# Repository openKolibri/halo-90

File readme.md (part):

![wornDynamic]

# HALO-90
A distinct ring of light. An ethereal glow. Patterns that ebb and flow to the music. Ninety lights. All controllable. Powered by a common coin cell. An engrossing look with retro vibes and a modern touch. This is HALO-90.

![presentedCase]

The *HALO* product series, in which these earrings ([HALO-90]) are the first item, is a fully open source electronic jewelery line. It is designed with elegance and wearability in mind. `90` refers to the ninety individually controllable LEDs on the earring face. The built-in compute power is also suitable for creating complex light shows.

This is the technical manual for anyone wanting to modify, hack, remix, or program their own light patterns onto the earrings. The manual goes into fine detail about construction, assembly, and firmware which should encompass all basic knowledge.

## Table of Contents
* [Design](#design)
  + [Hardware](#hardware)
    - [LEDs](#leds)
    - [Microcontroller](#microcontroller)
    - [Battery](#battery)
    - [Microphone](#microphone)
    - [Button](#button)
    - [IMU](#imu)
    - [Passives](#passives)
    - [Alignment Pins](#alignment-pins)
    - [Connectors](#connectors)
  + [Case](#case)
    - [FDM Printed](#fdm-printed)
    - [Cast](#cast)
      * [Mould Master](#mould-master)
      * [Silicone Mould](#silicone-mould)
    - [Stone Casting](#stone-casting)
    - [Magnets](#magnets)
* [Firmware](#firmware)
  + [Modes](#modes)
    - [Dynamic](#dynamic)
    - [Halo](#halo)
    - [Sparkle](#sparkle)
    - [Power Managment](#power-managment)
  + [LED control](#led-control)
  + [Compiling](#compiling)
    - [Ubuntu/WSL](#ubuntu-wsl)
    - [Arch](#arch)
  + [Flashing](#flashing)
    - [Windows](#windows)
    - [Linux](#linux)
* [Absolute Maximum Ratings](#absolute-maximum-ratings)
* [Guaranteed Ratings](#guaranteed-ratings)
* [Manufacturing](#manufacturing)
  + [BOM](#bom)
  + [PCB](#pcb)
  + [PCB Assembly](#pcb-assembly)
    - [Assembly Detail Pictures](#assembly-detail-pictures)
    - [Potential Alternates](#potential-alternates)
  + [Physical Assembly](#physical-assembly)
  + [Production Scaling](#production-scaling)
    - [Case](#case-1)
* [Programmer](#programmer)
* [Artwork](#artwork)
* [Inventory and QC](#inventory-and-qc)
* [Packaging](#packaging)
* [Shipping](#shipping)
* [Safety](#safety)
* [Certifications](#certifications)
* [Licence](#licence)
* [Attribution](#attribution)
  + [Fonts](#fonts)
  + [Libraries](#libraries)
* [ToDo](#todo)

## Design
Design was always a core objective from the very beginning. It *has* to look good. Even more importantly, it must also be functional, as it is a piece of jewelry people are going to wear. If it looks too complex or it's too difficult to use, no one will want to wear it. Comfort was also major goal, as heavy earrings are painful to wear for extended amounts of time, no matter how stunning they are. It's simply not worth the pain.

![render]

The design had to allow for a variety of LED patterns with a range from subtle to attention grabbing. Sensors were added to make light patterns more personal and reactive to the local environment, such as the muted audio responsive pattern. At one moment, befit for a quiet restaurant and later a flashy wide pattern at a concert.

| Audio        | Halo        | Sparkle        |
| ------------ | ----------- | -------------- |
| ![PAT-audio] | ![PAT-halo] | ![PAT-sparkle] |

### Hardware
The electronics are kept minimal for cost reduction and manufacturing simplicity with pads and routing done for all but the IMU and its pull-up resistors. They are not mounted, because there is no firmware support for that and it yields a lower cost variant. The design is done in [KiCad] 5.99 (nightly) and will be ported and set in the stable version. All components and libraries are embedded in the project. 

![IMG-schematic]

The schematic is also available as a [pdf][PDF-schematic]. The layout is done partially programmatically using text manipulation and template stamping using JavaScript and node and then finished up by hand in KiCad. The code is available [here][nodeHaloBuilding].

#### LEDs
There are 90 LEDs that make up the ring, All are regular `0402` red diodes. All the cathodes (K/-) face towards the center of the board, and are placed at `4°` intervals. The LEDS are charlieplexed with ten lines providing individual control. They are run at as high of a current as the battery's internal resistance and GPIO max current allows, so no resistors are used. The red LEDs, with their `2.0 V` - `2.6 V` forward voltage, permits maximizing battery usage
We are using [BL-HUB37A-AV-TRB], because it is low cost and has high availability across multiple vendors in China, but any `0402` LED with a V<sub>f</sub> below `2.7 V`, should yield an equivalent battery life.

![IMG-BL-HUB37A-AV-TRB]

#### Microcontroller
*STMicroelectonics's* [STM8L151G4] acts as the main controller for the earring. The low power microcontroller has a wide range of peripherals, a long expected production life, and low cost and availability in high quantities. Running at its max speed of `16 MHz` is able to easily charliplex the 90 Leds at over `1 kHz`. The `12b ADC` is used to readout the microphone and has plenty of flash (up to `32k`) to store an assortment of light patterns or complex processed designs.

![IMG-STM8151G6U6]

#### Battery
*Linx Technologies's* aptly named [BAT-HLD-001] is a stamped die-cut sheet-metal battery-holder that is as low profile as possible. It is sized for a `CR2032` lithium cell. The metal acts as the anode while the pad on the PCB is the cathode. Battery life varies based on what threshold for brightness you are content with. Over its lifetime, the internal resistance of the battery increases and the voltage decreases. This means that the current possible also decreases and thus the brightness.

![IMG-BAT-HLD-001]

#### Microphone
The microphone selection was rather difficult due to a lack of specifications available with amplified MEMS microphones. *Knowles* [SPW2430HR5H-B] was selected, as it seemed reasonable and could be tested with Adafruits breakout board fairly easily.

![IMG-SPW2430HR5H-B]

Using a built-in amplified MEMS microphone decreases the number of component placements and simplifies layout and verification, at the expense of not having instrumentation knowledge of your audio response.

#### Button
*C&K* [KXT3] series provides ultra low profile miniature tactile switches and we chose `KXT311LHS`, with a low actuation force of `100g`. It can be easily pressed with the edge of your nail, or a bit less comfortably with the back.

The button provides the functionality of changing light patterns by pressing and triggering it into a low power sleep mode by holding for `500 ms`. Completely available as an interrupt to the microcontroller, so other uses can be implemented. 

![IMG-KXT3]

#### IMU
[LSM6DSM] is a 6DOF IMU with a three-axis accelerometer and three-axis gyroscope by *STMicroelectronics*. It communicates over I2C and is connected to the hardware I2C peripheral in the microcontroller. It allows a fast data stream at very low power. It also has additional low power modes and the ability to wake the main microcontroller over interrupt with the routed interrupt pin. 

![IMG-LSM6DSM]

#### Passives
There are three passives (five if the IMU is populated) that can be of any tolerance. There are two `1 uF` and `0.1 uF` decoupling capacitors and one `10k` pull-up on the reset of the processor. The two IMU pull-ups are `10k` I2C pull-ups.

#### Alignment Pins
There are four tooling holes/alignment pins that can be used for add-ons. They are `1.152 mm` (`45.35 mil`) in diameter and are placed `2.8 mm` and `5.5 mm` from the center.

![alignmentPins]

 The earring is `24 mm` in diameter, has a mass of `5.207 g` (`2.135 g` without the battery) and the top eyelet extends `2 mm` extra, yielding a bounding box of `24 mm x 26 mm x 6.36 mm`.

![mass]

#### Connectors
The only connectors on the board are six `⌀ 1 mm` copper circles that are exposed as contacts for spring pins. They are placed evenly across the board so it receives balanced forces from the custom programmer (or testing jig).

| Labels      | Dimensions       |
| ----------- | ---------------- |
| ![pgrmPads] | ![pgrmPlacement] |

The labeled pins have their descriptions in the table below.

| Pin  | Description                      |
| ---- | -------------------------------- |
| 3V0  | Connected to Batt+ and power net |
| GND  | Connected to ground net          |
| TX   | GPIO PB2 for serial out          | 
| RX   | GPIO PB4 for serial in           | 
| RST  | Active low, 10k pull-up          | 
| SWIM | Programming interface            | 

### Case
The case holds the earrings and two cells in its cavities. This allows for the storing and organizing of at least 36 hours of available runtime. The earring case consists of two pieces held together with magnets. The cavities inside the case hold all components securely so that they do not rattle. The earrings are displayed beautifully when the case is opened.

![cases]

The case is designed in CAD and made to house two earrings (with or without batteries inserted) as well as two additional batteries. All of the edges are filleted and the closed case is comfortable when held. One corner is chamfered which makes it easier to align both pieces together in the correct orientation, and the magnets are oriented to resist trying to close it whenever the directionality does not match. It also provides a very satisfying tactile click when they align and close.

![caseRender]

#### FDM Printed
The first sets of cases are made of 3D printed plastic PLA. The top and bottom have bold contrasting colors that uniquely identify the brand. They are printed with a `20%` gyroid infill and at `200 um` layer height. The 3D models must be scaled up to `100.2%` to account for PLA shrinkage. 

![caseFDM]

#### Cast
For a more bold and distinctive style with a pebble or smooth seashell-like finish, casted cases provides an air of luxury using distinctive materials.

![caseBatch]

##### Mould Master
Moulding masters were made using the same 3D printed designs, printed at an `80 um` layer height, and then repeatedly filled, primed, and sanded with `P400` to `P3000` grit sandpaper on top of a glass plate to keep the straight faces square. This fills all of the air gaps and allows for a very smooth finish. It is then buffed to a shine with nail buffer sponges.

![caseMaster]

##### Silicone Mould
A platinum cure shore `A20` silicone rubber (Troll Factory [TYP-1]) is used to make a mould of the master. This has an accuracy of `~2 um` so it's able to reproduce a surface finish. Since the back is flat, an open-faced mould is made. The part, as well as the walls, are held in place with [Quakehold] museum wax, and mixing the exact amount of silicone needed (based on a CAD model) means a high yield. After curing, the mould box walls are cut off and the master is demoulded, yielding a silicone mould.

![caseMould]

#### Stone Casting
The mould can be cast with various materials, including other silicones, polyuretane, rubbers, and resins. In our case, we used plaster. We are using high compressive strength *Ernst Hinrichs* [Sockelgips FL] `Type-4 low expansion dental plaster`. These plasters have a thixotropic agent that allows them to flow better, which means that they mix thinner and reproduce in finer detail. Applying a surfactant to the mould, mixing with distilled water, and using a vibrating table produces castings with fewer bubbles. The back is roughly leveled off and set to cure. The part is demoulded and the back is hand finished with `P320-P3000` grit sandpaper.

![caseCasting]

After 24 hours, the part has cured to its final hardness and has dried out completely. It can then be processed further with magnets and dye. 

#### Magnets
The magnets are `6 mm x 1 mm` `N52` neodynium magnets that are glued in with UHU Max Repair Extreme adhesive. They are coated in `Ni-Cu-Ni`, at around `12 um`. The magnets are a very tight fit in their countersinks and are glued in to fit securely. They have a fixed orientation between both parts made, so swapping tops or bottoms with other sets is possible. There are few adhesives that work well when bonding two materials together that are already difficult to glue.

![6x1-magnets]

Magnets are installed using a gluing jig. One jig for the top and one for the bottom. Both jigs have magnets installed to correct for orientation when gluing. The jigs also have a matching chamfer which prevents the wrong part from being placed or placing the part backwards by accident.

![magnetsGlued]

The two jigs are color-coded as well. Adhesive is dispensed into the wells and the magnet is dropped, which automatically orients itself with the jig magnet. It can then be removed and set to cure.

![magnetJig]

## Firmware
The firmware is coded at the register level in C. The code is fully interrupt-based and performs quite efficiently. The toolchain is simple and built on open source tools. This makes it harder to code, but allows for significant optimization.
 
### Modes
There are multiple modes available on the halo earring that can be switched through when pressing the button. Each press of the button cycles to the next mode, eventually circling back around.

| Audio         | Halo        | Sparkle        |
| ------------- | ----------- | -------------- |
| ![GIF-audio]  | ![GIF-halo] | ![GIF-sparkle] |

#### Dynamic
The mode selected on startup is the audio-based dynamic mode. During every ADC cycle it reads the analog value and projects the audio waveform amplitude, based around a moving point on the ring with wrap around.

![PWR-audio]

Power profile readings show no correlation with audio level, and an `11.71 mA` power consumption with `105 uA` standard deviation. Projected battery life with a `220 mA` CR2032 cell is ~18.8 hours.

#### Halo
In the HALO mode, the entire light ring is lit. This is done through interlacing the illumination of each LED. The deep sleep auto wakeup timer is set to wake up every two clock cycles of the low speed `32 kHz` oscillator. On every wake, it changes to illuminate the 13th following LED, wrapping around at 90.

```c
setLed((prevLed + 13)%90);
```

This allows for a cleaner and more consistent scan over the entire halo ring since 13 is the greatest integer factor (besides 91), for all of the LEDs to be turned on evenly around the ring. Greater spacing causes *frames* to interlace with one another, resulting in a cleaner visual experience.

![PWR-halo]

Power profile readings show a `10.88 mA` power consumption with `60 uA` standard deviation. Projected battery life with a `220 mA` CR2032 cell is ~20.2 hours.

#### Sparkle
Sparkle mode is the best for minimal power draw and is implemented in a single line of code. At `~320 Hz`, the processor wakes from deep sleep and runs the selection of which LED to light (if any).

```c
rand()%15 ? ledLow(prevLed) : setLed(rand() % 90);
```

Given a 1/15 chance, a random LED will light up. Otherwise, any previously lit LEDs will be turned off. This results in a more visually pleasing pattern over just randomly lighting LEDs, which produce sharper bursts of light. Since the processor is only awake `0.002%` of the time, and the LED has a chance of being on only `6.6%` of the time, the power consumption is quite minimal. 

![PWR-sparkle]

Power profile readings show a `2.01 mA` power consumption with `327 uA` standard deviation. Projected battery life with a `220 mA` CR2032 cell is ~109.5 hours, (over 4.5 days).

#### Power Managment
Pressing and holding the button for `500 ms` will turn off all LEDs and put the cpu into deep sleep mode. In this mode the current draw is around `15 uA` and the only wake interrupt is the button press.

![GIF-boot]

Pressing and holding the button will show a boot-up animation that lights up in a ring around the face. Holding the button until it makes a full revolution, about one second, will trigger a software reset of the halo, turning it back on.

### LED control
Since the LEDs are configured in a charlieplex array, only one LED can be on at a time. Some optimization can allow multiple LEDs to light simultaneously, but at a cost of consistency in brightness and power draw. There are two low-level functions that can turn a individual LED on or off, as well as a helper function that remembers the last LED and turns it off before turning on the next one.

```c
void setLed(uint8_t led);
void ledHigh(uint8_t led);
void ledLow(uint8_t led);
```

The function to get the column and row from the LED number is shown below:
```c
uint8_t col = led / 9;
uint8_t topElements = 9 - col;
uint8_t row = 9 - (led % 9);
if (topElements <= (9 - row)) {
  row--;
}
```

To turn the LEDs off, the column and row are both set to high impedance. To turn it on, the column is set high and the row is set low.

The previous LED *must* be turned off before lighting up the next LED or else there is a risk of damaging the electronics. It is recommended to only use the `setLed` and `ledLow` functions.

### Compiling
Compiling is done with the [SDCC] ("Small Device C Compiler") and the included makefile.

As an example, the following steps are given for some systems but should easily be transferable to the distro of your choosing. The requirements are `make` and `sdcc`. They should both be available in the path. Once installation is completed, running `make` will generate the `halo.ihx` file, which is the binary to be flashed.

```bash
make
```

#### Ubuntu/WSL
```bash
sudo apt install -y make
sudo apt install -y sdcc
```
#### Arch
```bash
sudo pacman -S make
sudo pacman -S sdcc
```

### Flashing
Some form of flashing software is required, along with a programmer that can program over the `SWIM` protocol. We are using third party `STLink-V2` clones, because the form factor of the genuine programmer is difficult to use and newer programmers do not support `SWIM`.

#### Windows
`STVP_CmdLine` is required as the flashing software and comes with the software package [ST Visual Programmer]. This needs to be installed and `c/Program Files (x86)/STMicroelectronics/st_toolset/stvp/STVP_CmdLine.exe` needs to be added into the path.

Once it's installed, it can be run with the following flags. Preferably in WSL but should also be possible in CMD or PS.

```bash
STVP_CmdLine.exe -Device=STM8L15xG4 -FileProg=halo.ihx -verif -no_loop -no_log
```

It is also incorporated into the make file and can be run with the following:

```bash
make flash
```

#### Linux
[STM8 Flash] is an open source `SWIM` compatible flashing utility for linux. The tool is built from source. Short instructions are written below.

```bash
git clone https://github.com/vdudouyt/stm8flash.git
cd stm8flash
make
sudo make install
```

Flashing can then be done with the following command:

```bash 
stm8flash -cstlink -pstm8l151 -w halo.ihx
```

It is also incorporated into the make file and can be run with the following:

```bash
make flash
```

## Absolute Maximum Ratings

| Parameter         | Min  | Max | Unit |
| ----------------- | ----:| ---:| ---- |
| Battery Voltage   | -0.3 | 3.6 | Volt |
| Temperature       |  -40 |  85 | °C   |
| Power Draw        |  15u | 25m | Amp  |

## Guaranteed Ratings

| Parameter              | Min | Max | Unit |
| ---------------------- | ---:| ---:| ---- |
| Battery Voltage        | 1.8 | 3.6 | Volt |
| Operating Temperature  | -20 |  50 | °C   |
| Storage Temperature    | -40 |  85 | °C   |

The earrings should be fine to leave in a hot car (although the 3D printed plastic case could warp). If you are outside of these ratings, take care of yourself, you are either freezing or at risk of heat stroke. The earrings will be fine.

## Manufacturing
Although taking on novel uses of materials, the ability to manufacture at scale was always a primary focus. Parts were selected with strong supply chains and alternatives. Layout was designed with generous rules to accommodate for as many fabs as possible and the number of unique components was minimized. The microphone and battery holder are from single vendors but they have proven track records and well-known supply chains. Alternatives to be tested are still proposed.

### BOM
The BOM was selected with parts that are common to the high-volume Chinese manufacturing market, have strong supply chains, and have many alternatives available in case a supplier stops manufacture or supply dips occur. The number of unique parts was kept to a minimum and the maximum amount of features can be implemented with "free" pins, like the programming SMD pads. The table of BOM is shown below.

| REF    | QTY | Manufacturer              | MPN              | Description                         |
| ------ | ---:| ------------------------- | ---------------- | ----------------------------------- |
| D1-D90 |  90 | Brightled                 | BL-HUB37A-AV-TRB | LED: RED 627-637nm 50mcd@20mA 0402  |
| U1     |   1 | STMicroelectronics        | STM8L151G4U6     | MCU: 8b 16MHz 16k Flash UQFN-28-4x4 |
| MK1    |   1 | Knowles Electronics       | SPW2430HR5H-B    | MIC: Omni Si-Sonic 3.1x2.5x1.0mm    |
| BT1    |   1 | Linx Technologies         | BAT-HLD-001      | BAT: CR2032 Cell Holder             |
| S1     |   1 | C&K                       | KXT311LHS        | SW: Low Profile 3x2x0.6mm 100gf     |
| R3     |   1 | Uniroyal                  | 0402WGF1002TCE   | RES: 10k 5% 1/16W 0402              |
| C1     |   1 | Samsung Electro-Mechanics | CL05B104KO5NNNC  | CAP: MLCC 100nF 16V 0402            |
| C2     |   1 | Samsung Electro-Mechanics | CL05A105KA5NQNC  | CAP: MLCC 1uF 25V 0402              |

The [csv][BOMcsv] is provided with the sources.

### PCB
There is a single PCB. Although still common, some of the more precise requirements were needed to end up with a printed circuit board small enough.

| Parameter          | Value | Unit |
| ------------------ | -----:| ---- |
| Height             |    26 | mm   |
| Width              |    24 | mm   |
| Layers             |     4 | ul   |
| Copper             |   1.0 | oz   |
| Copper Inner       |   0.5 | oz   |
| Thickness          |   1.0 | mm   |
| Material           | FR4   | ul   |
| Min Drill          |   0.2 | mm   |
| Trace Size         |   5/5 | mil  |
| Mask               | Black | ul   |
| Silk               | White | ul   |
| E-Test             | Yes   | ul   |
| Surface Finish     | ENIG  | ul   |

The PCB has four layers.

| Front     | Inner 1   | Inner 2   | Back      |
| --------- | --------- | --------- | --------- |
| ![Layer0] | ![Layer1] | ![Layer2] | ![Layer3] |

### PCB Assembly
The whole board can be pick and placed. The table below shows some data that might be needed when requesting a quote.

| Parameter         | Value |
| ----------------- | -----:|
| Unique Parts      |     8 |
| SMD Parts         |     8 |
| Placements        |    97 |
| Solder Joints     |   222 |
| Front Components  |    96 |
| Back Components   |     1 |

The smallest components are `0402` LEDs, and all parts can survive normal lead-free re flow profiles. The microphone is open port MEMS so do not wash, clean, or expose it to ultrasonic vibrations (datasheet has further requirements).

#### Assembly Detail Pictures

| Assembly    | Front       |
| ----------- | ----------- |
| ![assembly] | ![front]    |

| Front Detail   | Back Detail   |
| -------------- | ------------- |
| ![frontDetail] | ![backDetail] |

| Front ISO   | Back ISO    |
| ----------- | ----------- |
| ![frontIso] | ![backIso]  |

#### Potential Alternates
Some alternates have not been tested, but their specifications match.

| Stated            | Alternative      | Tested |
| ----------------- | ---------------- | ------ |
| SPW2430HR5H-B     | ZILLTEK ZTS6016  | No     |
| BAT-HLD-001       | MY-2032-08       | No     |
| STM8L151G4U6      | STM8L151G6U*     | Yes    |

*To be updated when I can get stock or have to switch suppliers*

### Physical Assembly

The earwire is attached with jewelry pliers through the hole. The 1mm hole is made for up to `0.8 mm` wire over `20 ga`. Gold plated french hooks are used. these are commonly available as jewelry findings.

![IMG-frenchEarwire]

### Production Scaling Boards
The board can be hexagonally packed into a panel with tiny tabs since it's held on all sides. To increase production efficiency, only one side can be PnP and the battery holder is added afterwards by hand.

![hexPackedPanel]

#### Production Scaling Cases
The master moulds can create secondary masters out of resin which could then be used to make gang moulds, allowing for multiple castings in parallel. 

![gangMoulds]

## Programmer
The programmer has a hole at the top to allow a pin to push the button for testing.

![programmer]

The 3D printed base holds the board in place while the PCB is held to it with 3mm heat set inserts. The PCB acts as a compliant mechanism providing down pressure while still allowing it to be flexible enough to lift. 

The programmer uses *Mill-Max* ‎‎‎[0965-0-15-20-80-14-11-0]‎ spring pins on a PCB that matches exactly with the six pads on the face of the board. 

![springPins]

The top part is lifted up and the assembled board is slipped in. The spring force from the PCB pushes back down on to the pads and can then be left for programming and debugging.

## Artwork
The design and layout, the main artwork on the board and the PCB layers and traces, are *NOT* protected Intellectual Property ("IP"), see LICENSE files for appropriate details.
Any additional writing or images such as the Kolibri bird, copyright and designer notices, and certifications *ARE* considered protected IP and notice is given that they are protected by all applicable IP laws.
The below "Getting Started" card also has artwork which is considered protected IP and is copyrighted with all rights reserved.

| Front        | Back        |
| ------------ | ----------- |
| ![cardFront] | ![cardBack] | 

## Inventory and QC
Inventory can be managed with QR coded serialized tags. This serialization provides better quality control because it allows failure analysis and tracking in cases of issues traceable to batch and assembly.

## Packaging
We are packaging and shipping in `14 cm x 17 cm` padded envelopes with branded stampings. These fit under the Warenpost requirements and allow international shipping. The envelopes are verified to be under `3 cm` before dispatching. Custom labeled sleeves will be used for retail packaging.

## Shipping
The labels are printed with CN22 on the harmonized label schedule.

Lithium cells have special requirements for shipping. With air mail, small cells (up to four) are packaged securely and may be sent with the product. A note (`Lithium metal batteries in compliance with Section II of PI969`) is required on the packaging, but no warning label is mandatory.

For international shipping, the HS code `7117.90.0000	Imitation Jewlery other` is used.

## Safety
The edges are fully routed when possible or finished afterwards. The PCB is made from fiberglass so care must be taken because it can have abrasive edges. Clear coat nail polish can be applied to round and soften the edges without changing how it looks.

The `CR2032` cells are quite safe, as they have only very small traces of lithium, and have a fairly high internal resistance. However, they must still be disposed of responsibly. `LIR2032` or other rechargeable 2032 cells should *not* be used because they have a higher voltage outside of the guaranteed parameters and significantly lower capacity (under 25%).

If the battery is placed in backwards, it will drain over time because there is no reverse polarity protection. It will heat up but should not damage anything, due to high internal resistance limiting the discharge. The low voltage, `3.0 V`, as well as the currents used pose very little risk.

The printed circuit boards are assembled in a lead-free process, and all components are `ROHS` certified.

## Certifications
Certifications take time and effort but will make a better product by guaranteeing its safety to users and letting them use it in other projects. The table below shows the order in which we will obtain certifications.

| Certifying Authority     | Status                    |
| -------------------------| ------------------------- |
| OSHW                     | [DE000103]                |
| CE                       | No  (Self Certification)  |
| FCC                      | No  (Self Certification)  |
| WEEE                     | No  (yearly fee)          |

## Licence
The product was designed by Sawaiz Syed for Kolibri. Kolibri owns all protected IP. Everything that is not otherwise stated as being protected IP (e.g. firmware, PCB design, documentation) is released under permissive copyleft licenses.

| Sector        | License      | Version |
| ------------- | ------------ | -------:|
| Hardware      | [CERN-OHL-S] |     2.0 |
| Firmware      | [GNU GPL]    |     3.0 |
| Documentation | [CC BY-SA]   |     4.0 |

Files of all licenses are required with the distribution of files. All files are available in easy-to-modify formats for remixing. 

---
#### Please purchase original products from [Kolibri] to support further products, design, and research :)

---

## Attribution
- Make
- [SDCC]
- KiCad
- [STM8Flash]
### Fonts
- [Nunito]
- [IBM PLEX Mono]
- [DejaVu] 
### Libraries
- [STM8 Headers] Copyright (c) - 2020 Georg Icking-Konert

## ToDo
- [x] Led sometimes remains on after shutdown
- [x] Randomly HALO pattern forms high low pattern

<!--                       References                                      -->
<!-- Files -->
[BAT-HLD-001]:                ./pcb/components/BAT-HLD-001/BAT-HLD-001.pdf
[BL-HUB37A-AV-TRB]:           ./pcb/components/BL-HUB37A-AV-TRB/BL-HUB37A-AV-TRB.pdf
[KXT3]:                       ./pcb/components/KXT3/KXT3.pdf
[LSM6DSM]:                    ./pcb/components/LSM6DSM/LSM6DSM.pdf
[SPW2430HR5H-B]:              ./pcb/components/SPW2430HR5H-B/SPW2430HR5H-B.pdf
[STM8L151G4]:                 ./pcb/components/STM8151G6U6/STM8151G6U6.pdf
<!-- Links -->
[HALO-90]:                    https://openkolibri.com/hlo/90
[KiCad]:                      https://kicad.org/
[ST Visual Programmer]:       https://www.st.com/en/development-tools/stvp-stm32.html
[Quakehold]:                  https://www.quakehold.com/collectibles.html
[TYP-1]:                      https://trollfactory.de/produkte/silikon-kautschuk/haertegrad-shore/weich-shore-a25/7044/tfc-silikon-kautschuk-typ-1-abformsilikon-weich-1-1-nv-troll-factory-rtv
[0965-0-15-20-80-14-11-0]:    https://www.mill-max.com/products/pin/0965
[Sockelgips FL]:              https://www.hinrichs-dental-shop.de/sockelgips-fl-p-1469.html
[Kolibri]:                    https://openkolibri.com/
<!-- Internal Links -->
[PDF-schematic]:              ./docs/design/hardware/schematic.pdf        
[nodeHaloBuilding]:           ./pcb/halo.js
[BOMcsv]:                     ./pcb/bom.csv
<!-- Intro -->
[wornDynamic]:                ./docs/intro/wornDynamic.gif                              "Worn earring reacting to music Model: Greta"
[presentedCase]:              ./docs/intro/haloSetDisplay.jpg                           "Pair of earings in holder"
[render]:                     ./docs/render.jpg                                         "Render of earrings showing propertions"
<!-- Design -->
[PAT-audio]:                  ./docs/patterns/audio.gif                                 "Worn animation of audio pattern"
[PAT-halo]:                   ./docs/patterns/halo.gif                                  "Worn animation of halo pattern"
[PAT-sparkle]:                ./docs/patterns/sparkle.gif                               "Worn animation of sparkle pattern"
<!-- Hardware -->
[IMG-schematic]:              ./docs/design/hardware/schematic.png                      "Image of schematic"

<!-- Components -->
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
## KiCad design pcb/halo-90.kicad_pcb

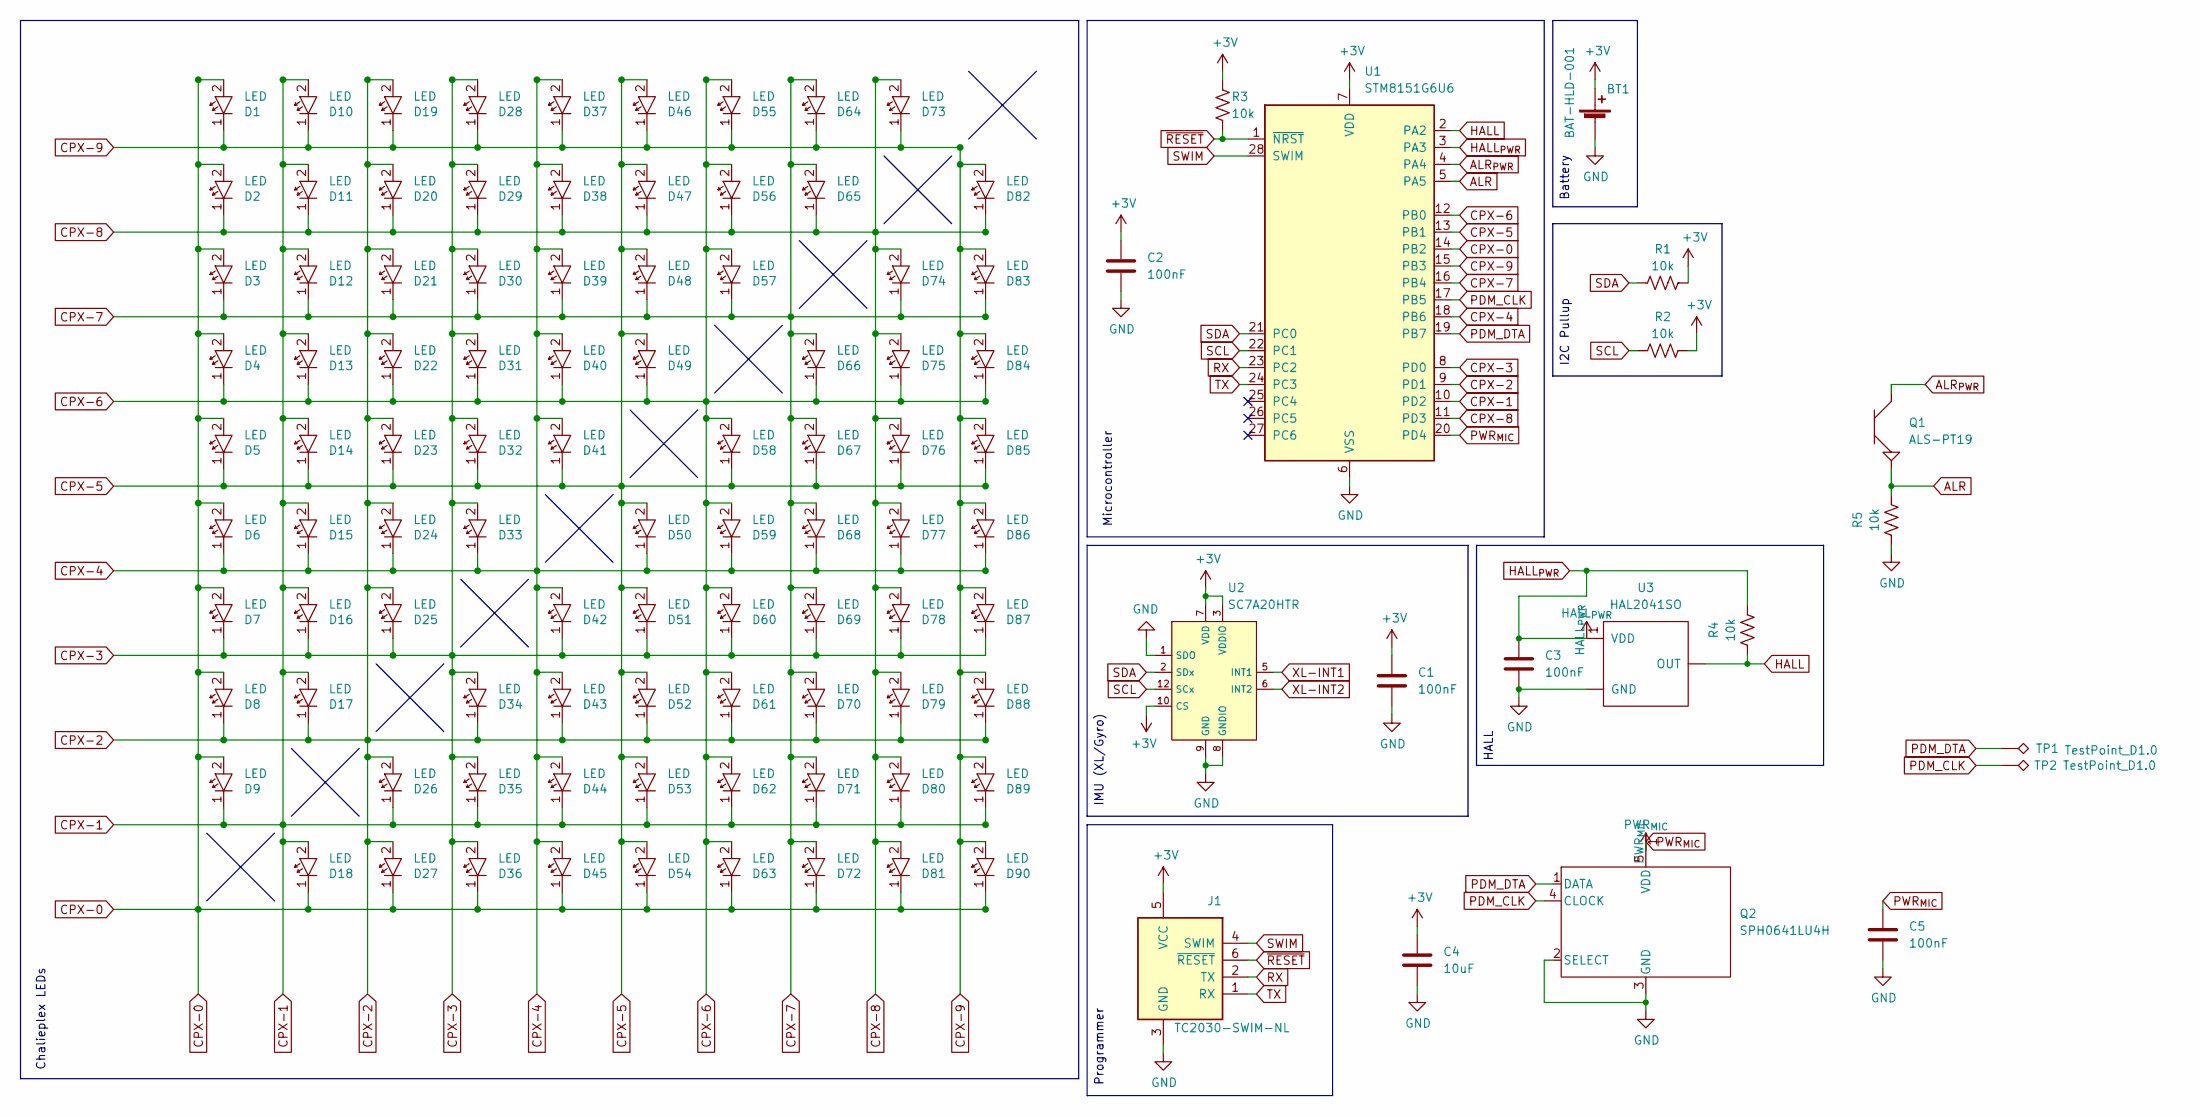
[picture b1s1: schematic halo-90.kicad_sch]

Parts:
BT1: BAT-HLD-001; LCSC Part # C7501066
C1, C2, C3, C5: 100nF; C-0402; MPN CL05B104KO5NNNC; LCSC Part # C1525
C4: 10uF; C-0402; MPN CL05A106MQ5NUNC; LCSC Part # C15525
D1, D2, D3, D4, D5, D6, D7, D8, D9, D10, D11, D12, D13, D14, D15, D16, D17, D18, D19, D20, D21, D22, D23, D24, D25, D26, D27, D28, D29, D30, D31, D32, D33, D34, D35, D36, D37, D38, D39, D40, D41, D42, D43, D44, D45, D46, D47, D48, D49, D50, D51, D52, D53, D54, D55, D56, D57, D58, D59, D60, D61, D62, D63, D64, D65, D66, D67, D68, D69, D70, D71, D72, D73, D74, D75, D76, D77, D78, D79, D80, D81, D82, D83, D84, D85, D86, D87, D88, D89, D90: LED; XL-1005SURC; MPN XL-1005SURC; LCSC Part # C25503345
J1: TC2030-SWIM-NL; TC2030-IDC-NL
Q1: ALS-PT19; MPN ALS-PT19-315C/L177/TR8; LCSC Part # C146233
Q2: SPH0641LU4H; MPN SPH0641LU4H-1; LCSC Part # C2879853
R1, R2, R3, R4, R5: 10k; R-0402; MPN 0402WGF1002TCE; LCSC Part # C25744
TP1, TP2: TestPoint_D1.0; TestPoint_Pad_D1.0mm
U1: STM8151G6U6; UFQFPN28; MPN STM8151G6U6; LCSC Part # C85325
U2: SC7A20HTR; MPN SC7A20HTR; LCSC Part # C19274408
U3: HAL2041SO; MPN HAL2041SO; LCSC Part # C22400320

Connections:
+3V: BT1.1 (+), C1.1, C2.1, C4.1, J1.5 (VCC), R1.2, R2.2, R3.1, U1.7 (VDD), U2.3 (VDDIO), U2.7 (VDD), U2.10 (CS)
ALR: Q1.2 (Emitter), R5.2, U1.5 (PA5)
ALR_{PWR}: Q1.1 (Collector), U1.4 (PA4)
CPX-0: D1.2 (K), D2.2 (K), D3.2 (K), D4.2 (K), D5.2 (K), D6.2 (K), D7.2 (K), D8.2 (K), D9.2 (K), D18.1 (A), D27.1 (A), D36.1 (A), D45.1 (A), D54.1 (A), D63.1 (A), D72.1 (A), D81.1 (A), D90.1 (A), U1.14 (PB2)
CPX-1: D9.1 (A), D10.2 (K), D11.2 (K), D12.2 (K), D13.2 (K), D14.2 (K), D15.2 (K), D16.2 (K), D17.2 (K), D18.2 (K), D26.1 (A), D35.1 (A), D44.1 (A), D53.1 (A), D62.1 (A), D71.1 (A), D80.1 (A), D89.1 (A), U1.10 (PD2)
CPX-2: D8.1 (A), D17.1 (A), D19.2 (K), D20.2 (K), D21.2 (K), D22.2 (K), D23.2 (K), D24.2 (K), D25.2 (K), D26.2 (K), D27.2 (K), D34.1 (A), D43.1 (A), D52.1 (A), D61.1 (A), D70.1 (A), D79.1 (A), D88.1 (A), U1.9 (PD1)
CPX-3: D7.1 (A), D16.1 (A), D25.1 (A), D28.2 (K), D29.2 (K), D30.2 (K), D31.2 (K), D32.2 (K), D33.2 (K), D34.2 (K), D35.2 (K), D36.2 (K), D42.1 (A), D51.1 (A), D60.1 (A), D69.1 (A), D78.1 (A), D87.1 (A), U1.8 (PD0)
CPX-4: D6.1 (A), D15.1 (A), D24.1 (A), D33.1 (A), D37.2 (K), D38.2 (K), D39.2 (K), D40.2 (K), D41.2 (K), D42.2 (K), D43.2 (K), D44.2 (K), D45.2 (K), D50.1 (A), D59.1 (A), D68.1 (A), D77.1 (A), D86.1 (A), U1.18 (PB6)
CPX-5: D5.1 (A), D14.1 (A), D23.1 (A), D32.1 (A), D41.1 (A), D46.2 (K), D47.2 (K), D48.2 (K), D49.2 (K), D50.2 (K), D51.2 (K), D52.2 (K), D53.2 (K), D54.2 (K), D58.1 (A), D67.1 (A), D76.1 (A), D85.1 (A), U1.13 (PB1)
CPX-6: D4.1 (A), D13.1 (A), D22.1 (A), D31.1 (A), D40.1 (A), D49.1 (A), D55.2 (K), D56.2 (K), D57.2 (K), D58.2 (K), D59.2 (K), D60.2 (K), D61.2 (K), D62.2 (K), D63.2 (K), D66.1 (A), D75.1 (A), D84.1 (A), U1.12 (PB0)
CPX-7: D3.1 (A), D12.1 (A), D21.1 (A), D30.1 (A), D39.1 (A), D48.1 (A), D57.1 (A), D64.2 (K), D65.2 (K), D66.2 (K), D67.2 (K), D68.2 (K), D69.2 (K), D70.2 (K), D71.2 (K), D72.2 (K), D74.1 (A), D83.1 (A), U1.16 (PB4)
CPX-8: D2.1 (A), D11.1 (A), D20.1 (A), D29.1 (A), D38.1 (A), D47.1 (A), D56.1 (A), D65.1 (A), D73.2 (K), D74.2 (K), D75.2 (K), D76.2 (K), D77.2 (K), D78.2 (K), D79.2 (K), D80.2 (K), D81.2 (K), D82.1 (A), U1.11 (PD3)
CPX-9: D1.1 (A), D10.1 (A), D19.1 (A), D28.1 (A), D37.1 (A), D46.1 (A), D55.1 (A), D64.1 (A), D73.1 (A), D82.2 (K), D83.2 (K), D84.2 (K), D85.2 (K), D86.2 (K), D87.2 (K), D88.2 (K), D89.2 (K), D90.2 (K), U1.15 (PB3)
GND: BT1.2 (-), C1.2, C2.2, C3.2, C4.2, C5.2, J1.3 (GND), Q2.2 (SELECT), Q2.3 (GROUND), R5.1, U1.6 (VSS), U2.1 (SDO), U2.8 (GNDIO), U2.9 (GND), U3.3 (GND)
HALL: R4.1, U1.2 (PA2), U3.2 (OUT)
HALL_{PWR}: C3.1, R4.2, U1.3 (PA3), U3.1 (VCC)
PDM_CLK: Q2.4 (CLOCK), TP2.1 (1_1), U1.17 (PB5)
PDM_DTA: Q2.1 (DATA), TP1.1 (1_1), U1.19 (PB7)
PWR_{MIC}: C5.1, Q2.5 (V_{DD}), U1.20 (PD4)
RX: J1.2 (TX), U1.23 (PC2)
SCL: R2.1, U1.22 (PC1), U2.12 (SCx)
SDA: R1.1, U1.21 (PC0), U2.2 (SDx)
SWIM: J1.4 (SWIM), U1.28 (SWIM)
TX: J1.1 (RX), U1.24 (PC3)
XL-INT1: U2.5 (INT1)
XL-INT2: U2.6 (INT2)
~RESET: J1.6 (~RESET), R3.2, U1.1 (~NRST)

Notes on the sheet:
IMU (XL/Gyro)
Battery
Microcontroller
HALL
I2C Pullup
Chalieplex LEDs
Programmer

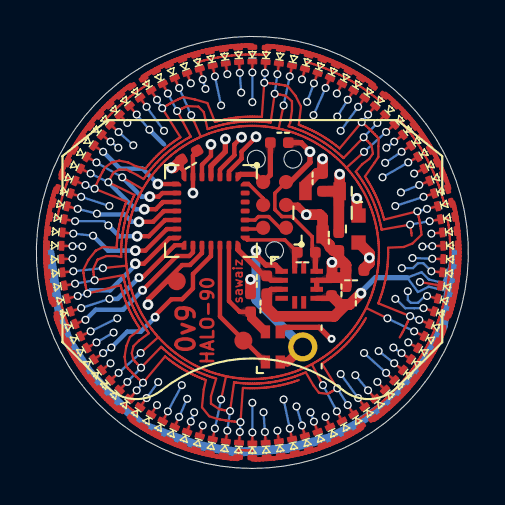
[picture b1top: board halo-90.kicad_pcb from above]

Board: 4 copper layers, 24.0 x 24.0 mm, 109 parts (1 on the bottom side), 25 nets.

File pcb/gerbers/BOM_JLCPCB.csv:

"Comment","Designator","Footprint","LCSC Part #"
"CR-2032","BT1","BAT-HLD-001:BAT-HLD-001","C7501066"
"10uF","C4","C-0402:C-0402","C15525"
"100nF","C1,C2,C3","C-0402:C-0402","C1525"
"LED","D1,D2,D3,D4,D5,D6,D7,D8,D9,D10,D11,D12,D13,D14,D15,D16,D17,D18,D19,D20,D21,D22,D23,D24,D25,D26,D27,D28,D29,D30,D31,D32,D33,D34,D35,D36,D37,D38,D39,D40,D41,D42,D43,D44,D45,D46,D47,D48,D49,D50,D51,D52,D53,D54,D55,D56,D57,D58,D59,D60,D61,D62,D63,D64,D65,D66,D67,D68,D69,D70,D71,D72,D73,D74,D75,D76,D77,D78,D79,D80,D81,D82,D83,D84,D85,D86,D87,D88,D89,D90","XL-1005SURC:XL-1005SURC","C25503345"
"TC2030-SWIM-NL","J1","TC2030-IDC-NL:TC2030-IDC-NL",""
"10k","R1,R2,R3,R4","R-0402:R-0402","C25744"
"STM8151G6U6","U1","STM8151G6U6:UFQFPN28","C85325"
"SC7A20HTR","U2","SC7A20HTR:SC7A20HTR","C19274408"
"HAL2041SO","U3","HAL2041SO:HAL2041SO","C22400320"

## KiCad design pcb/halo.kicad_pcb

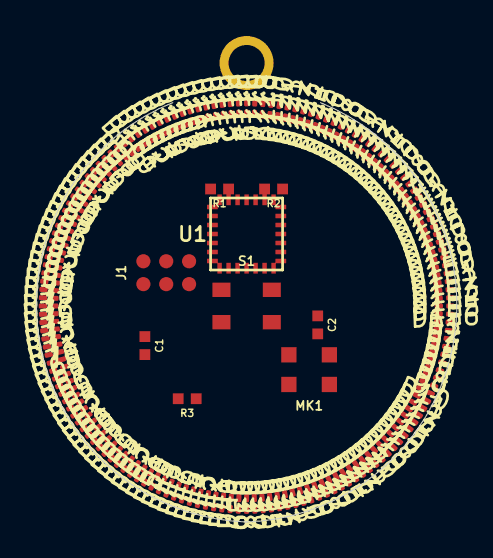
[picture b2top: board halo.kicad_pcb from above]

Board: 4 copper layers, 23.4 x 23.3 mm, 166 parts (0 on the bottom side), 22 nets, no tracks yet.

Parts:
C1, C2: C-0402
D1, D2, D3, D4, D5, D6, D7, D8, D9, D10, D11, D12, D13, D14, D15, D16, D17, D18, D19, D20, D21, D22, D23, D24, D25, D26, D27, D28, D29, D30, D31, D32, D33, D34, D35, D36, D37, D38, D39, D40, D41, D42, D43, D44, D45, D46, D47, D48, D49, D50, D51, D52, D53, D54, D55, D56, D57, D58, D59, D60, D61, D62, D63, D64, D65, D66, D67, D68, D69, D70, D71, D72, D73, D74, D75, D76, D77, D78, D79, D80, D81, D82, D83, D84, D85, D86, D87, D88, D89, D90, D91, D92, D93, D94, D95, D96, D97, D98, D99, D100, D101, D102, D103, D104, D105, D106, D107, D108, D109, D110, D111, D112, D113, D114, D115, D116, D117, D118, D119, D120, D121, D122, D123, D124, D125, D126, D127, D128, D129, D130, D131, D132, D133, D134, D135, D136, D137, D138, D139, D140, D141, D142, D143, D144, D145, D146, D147, D148, D149, D150, D151, D152, D153, D154, D155, D156: LED; LED_0201_0603Metric
H1: TestPoint_Pad_D4.0mm
J1: Tag-Connect_TC2030-IDC-NL_2x03_P1.27mm_Vertical
MK1: ZTS6216
R1, R2, R3: R-0402
S1: TS-1088-AR02016
U1: STM8L151G6; UFQFPN28

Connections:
+3V: C1.1, C2.1, J1.1, R3.1, U1.7
CPX-0: D1.1, D2.1, D3.1, D4.1, D5.1, D6.1, D7.1, D8.1, D9.1, D10.1, D11.1, D12.1, D13.2, D25.2, D37.2, D49.2, D61.2, D73.2, D85.2, D97.2, D109.2, D121.2, D133.2, D145.2, R1.2, U1.22
CPX-1: D1.2, D13.1, D14.1, D15.1, D16.1, D17.1, D18.1, D19.1, D20.1, D21.1, D22.1, D23.1, D24.1, D26.2, D38.2, D50.2, D62.2, D74.2, D86.2, D98.2, D110.2, D122.2, D134.2, D146.2, R2.2, U1.21
CPX-2: D2.2, D14.2, D25.1, D26.1, D27.1, D28.1, D29.1, D30.1, D31.1, D32.1, D33.1, D34.1, D35.1, D36.1, D39.2, D51.2, D63.2, D75.2, D87.2, D99.2, D111.2, D123.2, D135.2, D147.2, U1.27
CPX-3: D3.2, D15.2, D27.2, D37.1, D38.1, D39.1, D40.1, D41.1, D42.1, D43.1, D44.1, D45.1, D46.1, D47.1, D48.1, D52.2, D64.2, D76.2, D88.2, D100.2, D112.2, D124.2, D136.2, D148.2, U1.18
CPX-4: D4.2, D16.2, D28.2, D40.2, D49.1, D50.1, D51.1, D52.1, D53.1, D54.1, D55.1, D56.1, D57.1, D58.1, D59.1, D60.1, D65.2, D77.2, D89.2, D101.2, D113.2, D125.2, D137.2, D149.2, U1.17
CPX-5: D5.2, D17.2, D29.2, D41.2, D53.2, D61.1, D62.1, D63.1, D64.1, D65.1, D66.1, D67.1, D68.1, D69.1, D70.1, D71.1, D72.1, D78.2, D90.2, D102.2, D114.2, D126.2, D138.2, D150.2, U1.14
CPX-6: D6.2, D18.2, D30.2, D42.2, D54.2, D66.2, D73.1, D74.1, D75.1, D76.1, D77.1, D78.1, D79.1, D80.1, D81.1, D82.1, D83.1, D84.1, D91.2, D103.2, D115.2, D127.2, D139.2, D151.2, U1.16
CPX-7: D7.2, D19.2, D31.2, D43.2, D55.2, D67.2, D79.2, D85.1, D86.1, D87.1, D88.1, D89.1, D90.1, D91.1, D92.1, D93.1, D94.1, D95.1, D96.1, D104.2, D116.2, D128.2, D140.2, D152.2, U1.15
CPX-8: D8.2, D20.2, D32.2, D44.2, D56.2, D68.2, D80.2, D92.2, D97.1, D98.1, D99.1, D100.1, D101.1, D102.1, D103.1, D104.1, D105.1, D106.1, D107.1, D108.1, D117.2, D129.2, D141.2, D153.2, U1.13
CPX-9: D9.2, D21.2, D33.2, D45.2, D57.2, D69.2, D81.2, D93.2, D105.2, D109.1, D110.1, D111.1, D112.1, D113.1, D114.1, D115.1, D116.1, D117.1, D118.1, D119.1, D120.1, D130.2, D142.2, D154.2, U1.12
CPX-10: D10.2, D22.2, D34.2, D46.2, D58.2, D70.2, D82.2, D94.2, D106.2, D118.2, D121.1, D122.1, D123.1, D124.1, D125.1, D126.1, D127.1, D128.1, D129.1, D130.1, D131.1, D132.1, D143.2, D155.2, U1.19
CPX-11: D11.2, D23.2, D35.2, D47.2, D59.2, D71.2, D83.2, D95.2, D107.2, D119.2, D131.2, D133.1, D134.1, D135.1, D136.1, D137.1, D138.1, D139.1, D140.1, D141.1, D142.1, D143.1, D144.1, D156.2, U1.20
CPX-12: D12.2, D24.2, D36.2, D48.2, D60.2, D72.2, D84.2, D96.2, D108.2, D120.2, D132.2, D144.2, D145.1, D146.1, D147.1, D148.1, D149.1, D150.1, D151.1, D152.1, D153.1, D154.1, D155.1, D156.1, U1.23
GND: C1.2, C2.2, J1.3, MK1.2, MK1.3, S1.3, S1.4, U1.6
MIC: MK1.1, R1.1, U1.3
MIC_PWR: MK1.4, R2.1, U1.4
RST: J1.4, R3.2, U1.1
RX: J1.6, U1.9
SW: S1.1, S1.2, U1.5
SWIM: J1.2, U1.28
TX: J1.5, U1.8

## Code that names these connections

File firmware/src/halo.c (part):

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// Q8 reciprocal of bass_extent (256/extent), precomputed at 24 Hz so the
// render ISR can turn glow_dist into a 0..255 radial without a divide.
volatile uint8_t bass_inv_extent_q8 = 0;
volatile uint8_t mic_warmup = 0;          // Frames until the PDM mic's modulator output is trusted

// The USART has a single-byte buffer and mic captures blank the main loop
// for up to 18 ms while shell characters arrive 1 ms apart: capture loops
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volatile uint8_t spark_life[SPARK_COUNT] = {0, 0, 0, 0};

// xlMic (0v9) board pinout, extracted from pcb/halo-90.kicad_pcb:
//   Accelerometer SC7A20HTR (I2C): SDA PC0, SCL PC1.
//     INT1/INT2 are NOT routed to the MCU on this revision.
//   Hall HAL2041S: OUT on PA2 (EXTI2 wake), VCC power-gated by PA3.
//   ALR (ambient light): sense on PA5, power-gated by PA4. Unused for now.
//   PDM microphone: CLK PB5, DATA PB7, power-gated by PD4. Unused for now.
//   UART: TX PC3, RX PC2. SWIM pin 28. PC4-PC6 unconnected.

// Charlieplex lines CPX-0..CPX-9 (net names in the PCB):
//   0=PB2 1=PD2 2=PD1 3=PD0 4=PB6 5=PB1 6=PB0 7=PB4 8=PD3 9=PB3
PORT_t *CPX_PORT[] = {&sfr_PORTB, &sfr_PORTD, &sfr_PORTD, &sfr_PORTD,
                      &sfr_PORTB, &sfr_PORTB, &sfr_PORTB, &sfr_PORTB,
                      &sfr_PORTD, &sfr_PORTB};
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  cpx_group_enabled = cpxLayoutSafe();

  // Unused xlMic peripherals held off and quiet (awake and asleep):
  // mic power gate PD4 low, PDM_CLK PB5 / PDM_DTA PB7 driven low (the
  // unpowered mic never contends), ALR power gate PA4 low and its sense
  // node PA5 driven low while unpowered. No pin is left floating.
  sfr_PORTD.ODR.byte &= ~PIN4;
  sfr_PORTD.DDR.byte |= PIN4;
  sfr_PORTB.ODR.byte &= ~(PIN5 | PIN7);
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      }

      // Disable UART explicitly to prevent back-powering any connected serial bridges!
      // PC3 = TX. We must disable transmitter and set pin to Output LOW or Floating to kill the 1.2mA leak.
      sfr_USART1.CR2.TEN = 0;
      sfr_USART1.CR2.REN = 0;
      sfr_PORTC.ODR.byte &= ~(1<<3);
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      sfr_PORTC.DDR.byte |= (1<<3);

      // On this board the accel INT pins are not routed to the MCU. The
      // mic (PWR_MIC PD4, PDM PB5/PB7) and ALR (ALR_PWR PA4, sense PA5)
      // rails are held off / driven low permanently from boot, so nothing
      // floats here. HALL_PWR (PA3) stays high through HALT - the hall
      // sensor is the wake source and GPIO state is retained in halt.

      // Sleep power budget with this configuration (typical, 25 C, 3.0 V):
      //   STM8L151 HALT, ULP=1 (internal ref off), Flash/EEPROM power-down:
      //     ~0.35 uA
      //   SC7A20 power-down (CTRL1 = 0x00):              ~0.5 uA
      //   Hall switch (powered via PA3 - the wake source): ~1-2 uA class
      //   Mic and ALR power-gated off:                     ~0 uA
      //   GPIO leakage with every pin driven or pulled:   <0.1 uA
      //   => ~0.9 uA for MCU + accel; ~2-3 uA system with the hall sensor.
      // I2C pull-ups (PC0/PC1) stay enabled: both lines idle high against
      // the sensor's high-Z pads, so they carry no static current. UART RX
      // (PC2) keeps its pull-up for a defined level with no bridge attached.
      // Wake is the PA2 EXTI2 edge from the hall output; no clocks run in HALT.

      // Ensure EXTI flags are clear before entering halt loop
      sfr_ITC_EXTI.SR1.P2F = 1;
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}

void initHall(void){
  // HALL_PWR (PA3) high: the hall sensor is GPIO power-gated on this board
  // and must stay powered through HALT - it is the wake source. GPIO state
  // is retained in halt, so this costs only the sensor's own current.
  sfr_PORTA.ODR.byte |= PIN3;
  sfr_PORTA.CR1.byte |= PIN3;
  sfr_PORTA.DDR.byte |= PIN3;

  // Hall output on PA2
  sfr_PORTA.DDR.byte &= ~PIN2; // Input
  sfr_PORTA.CR1.byte |= PIN2;  // Pull-up
  sfr_PORTA.CR2.byte |= PIN2;  // Interrupt enabled
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  // Reset peripheral before re-enabling
  sfr_I2C1.CR1.PE = 0;

  // Set PC0/PC1 as Inputs, WITH Internal Pull-Ups enabled.
  // The HW schematic lacks external pull-ups; I2C will fail without this.
  sfr_PORTC.DDR.byte &= ~((1<<0) | (1<<1));
  sfr_PORTC.CR1.byte |= ((1<<0) | (1<<1));
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}

// ---- PDM microphone over SPI1 ----
// The xlMic board routes the PDM mic onto SPI1's natural pins: PDM_CLK is
// PB5 (SPI1_SCK) and PDM_DTA is PB7 (SPI1_MISO). Running SPI1 as a master
// in receive-only mode turns SCK into a free-running 1 MHz PDM clock
// (16 MHz / 16, within the mic's 1.0-3.25 MHz spec) while the mic's 1-bit
// sigma-delta stream arrives in DR a byte at a time. Receive-only mode
// never drives MOSI, so PB6 (charlieplex line CPX-4) is untouched.
// No decimation filter fits this MCU comfortably; instead each burst is
// reduced to ones-density statistics: silence sits near 50 percent density,
// a stuck data line reads 0 or 100 percent, and audio shows up as density
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#define MIC_SUB_BLOCKS 8        // 8 sub-blocks = 1920 bits = 1.92 ms at 1 MHz

void micPowerOn(void) {
  sfr_PORTD.ODR.byte |= PIN4;   // PWR_MIC on
  sfr_PORTB.DDR.byte &= ~PIN7;  // PDM_DTA -> MISO input, mic drives it
  sfr_PORTB.CR1.byte &= ~PIN7;
  // PDM_CLK -> SCK push-pull, fast slope. DDR before CR2: on an input pin
  // CR2 is the external-interrupt enable, and PB5 has no handler - setting
  // it even momentarily while the pin is still an input hangs the MCU on
  // an unhandled vector.
  sfr_PORTB.ODR.byte &= ~PIN5;
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  sfr_CLK.PCKENR1.PCKEN14 = 1;  // SPI1 clock
  sfr_SPI1.CR1.byte = 0;
  sfr_SPI1.CR2.byte = 0;
  sfr_SPI1.CR2.SSM = 1;         // no NSS pin: PB4 stays a charlieplex line
  sfr_SPI1.CR2.SSI = 1;
  sfr_SPI1.CR2.RXONLY = 1;      // clock runs while SPE=1; MOSI never driven
  sfr_SPI1.CR1.BR = 3;          // 16 MHz / 16 = 1 MHz
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void micPowerOff(void) {
  sfr_SPI1.CR1.SPE = 0;
  sfr_CLK.PCKENR1.PCKEN14 = 0;
  sfr_PORTD.ODR.byte &= ~PIN4;  // PWR_MIC off
  // Park both PDM lines driven low again (unpowered mic never contends)
  sfr_PORTB.DDR.byte |= (PIN5 | PIN7); // outputs first
  sfr_PORTB.CR2.byte &= ~PIN5;         // then drop the slope/EXTI bit
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
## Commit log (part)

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2021-01-17 inital docs commit
2021-01-19 Slowly, I've been close for hours../..
2021-02-02 Added more to the readme
2021-02-03 Moved earwire andded to docs
2021-02-03 More docs
2021-02-03 Fixed earwire img
2021-02-15 Docs improvment
2021-02-15 Added case info
2021-02-15 Picture proprtions
2021-02-17 Update readme.md
    Edits up to button
2021-02-17 Update readme.md
    Up until FDM printed
2021-02-22 Added spring pin part
2021-02-22 Added gifs to readme
2021-02-22 Docs addtions
2021-02-22 fixed pgrm aspect ratio
2021-02-22 Added power profile
2021-02-22 update docs
2021-02-22 Add docs licence file
2021-02-23 Update readme.md
    GIF-boot to Programmer
2021-02-23 Update readme.md
    Programmer to end
2021-02-23 Docs
2021-02-23 Docs 98% done
2021-02-24 Update readme.md
    Full read thru
2021-02-26 Update readme.md
    Correction
2021-03-02 Fixed spelling, notes from @camille-vanhoffelen
2021-03-03 added OSHWA cetificatoin
2021-04-20 Cleanup and clarification by native en-US speaker
2023-11-28 Fix some typos
2024-01-15 fix: makefile: Autodetect installed commands didn't work
    The makefile command `$(command …)` did not work as expected and
    returned always nothing. Only by appending `shell` the command gets
    actually executed and is able to return a path if the command is
    available.
2024-01-15 feat: Setup better build system with Make
    This allows us to have multiple files and a build directory, which makes
    cleaning significantly easier in the long run.
    Also introduced debug build which generates a .elf file
2025-01-27 Added case files
2025-03-12 Added earring case modified for FishHook ear wires
2026-02-04 0v7 sent to JLC
2026-02-20 docs(firmware): clean up halo.c code and add comments
    - Fix spelling errors including 'interupt', 'inefficent', 'unil'
    - Add explanation of charlieplexing pin mapping algorithm
    - Add module description header to halo.c
2026-02-20 feat(pcb): update LED footprint to trapezoidal pad and apply JLCPCB 4-layer 0.8mm design rules
    - Updated BL-HUB37A-AV-TRB:D-0402 to use trapezoidal pads optimally shaped for a radial/circular array.
    - Injected updated 90 D-0402 footprint instances into halo-90.kicad_pcb.
    - Updated via specs to 0.45mm / 0.25mm to meet JLC standard 4-layer capabilities.
    - Defined 0.1mm minimum clearance and track width in halo-90.kicad_pro.
    - Verified 0.8mm board thickness is active in the PCB settings.
2026-02-20 feat(pcb): standardize component footprints across the board to IPC design rules
    - Set all courtyard line widths (`F.CrtYd` and `B.CrtYd`) strictly to 0.05 mm.
    - Enforced minimum silkscreen width > 0.12 mm for robust fab readability.
    - Embedded a generic "Generic component footprint" description tag if missing on components.
    - Appended `(attr smd)` correctly onto all non-THT components in Kicad libraries.
    - Re-injected all footprint updates seamlessly into `halo-90.kicad_pcb`.
2026-02-20 pcb: upgrade to KiCad 9 format with elegant curved fan-out routing
    - Synchronized netlist with schematic source of truth
    - Implemented mathematically elegant circular arc trace paths in halo.js
    - Standardized symbol libraries and PCB format to KiCad 9 (20241229)
    - Corrected gr_arc syntax and added mandatory timestamps for segments/vias
    - Updated README.md with design intentions and programmatic layout details
2026-02-20 pcb: aesthetic redesign with circular fan-out as jewelry artwork
    - Restored original component placements (Button S1, Mic MK1, MCU U1 at 0,-4)
    - Implemented high-resolution circular spiral routing for MCU fan-out
    - Reduced trace width to 0.1mm and de-cluttered reference text
    - Added 3D model STP references for LEDs and MCU
    - Verified netlist and KiCad 9 compatibility
2026-02-24 Update design to 156 Charlieplexed 0201 LEDs and clean up repository
2026-02-24 Remove old 90 LED files
2026-02-24 Update constraints to 4-layer 0.09mm, patch ERC pad types, resolve LED radial collisions by slimming pads to 0.28mm width, fix MCU absolute rotation logic
2026-03-02 To explore later, current save
2026-03-04 WIP: Current hardware updates
2026-03-04 added build to gitignore
2026-03-06 Acceleometer shcematic done?
2026-03-07 Updated trace widths.
2026-03-07 Manufacturing: Apply JLCPCB 4-layer 0.8mm specifications and clean DRC
    * Updated `.kicad_pro` to enforce 4-layer 0.8mm specs:
    - Minimum clearance & trace width: 0.09mm
    - Minimum via: 0.45mm diameter / 0.25mm drill (Defaulted manually to 0.45/0.3)
    - Default Silkscreen: 0.8mm x 0.8mm x 0.15mm
    - Power net class added for routing
    * Cleaned up DRC errors in `.kicad_pcb`:
2026-03-07 Manufacturing: Inline LCSC attributes into BOM and purge legacy DRC logs
    - Added 'LCSC Part #' tracking directly natively to the project 'bom.csv'.
    - Cleaned up obsolete 'drc_report*.txt' debugging exports from the working tree.
2026-03-07 Manufacturing: Finalize KiCad Schematics and Repackage Production Files
    - Fixed 94 ERC output pin conflicts by redefining LED:BL-HUB37A symbols electrically as 'Passive'.
    - Removed erroneous 'No Connect' markers from 11 actively routed STM8L GPIO pins.
    - Suppressed schematic localized library mismatch warnings due to LED pin alterations.
    - Deleted outdated manual 'bom.csv' in favor of the dynamic 'gerbers/BOM_JLCPCB.csv' source of truth.
    - Regenerated final Gerber/Drill manufacturing files and packaged 'gerbers.zip'.
2026-03-08 fix(pcb): update STM MCU, reformat BOM and PnP files
    - Replaced STM8L15xxx with STM8151G6U6 in symbols, footprints, directories, and documentation
    - Assigned JLCPCB part number C85325 to the new MCU in the schematic
    - Scaled CPL pick & place coordinates to millimeters so JLC doesn't position everything at parsing origin
    - Grouped BOM by footprint/values matching JLCPCB format
    - Generated updated gerbers.zip
2026-03-08 fix(pcb): update JLCPCB BOM component LCSC parts
    - Set BT1 (CR2032 holder) to C70377
    - Set U3 (DRV5032) to C130005
    - Set D1-D90 (0402 LEDs) to C198650
    - Renamed 100n capacitors to 100nF for JLC verification match
    - Regenerated BOM and Gerbers archive
2026-03-08 fix(pcb): remove silkscreen and markings from all footprints except for LED and Battery
2026-03-08 fix(pcb): final component property fixes for JLCPCB
    - U3 swapped to HAL2041SO (C22400320)
    - BT1 reverted to BAT-HLD-001 (C7501066)
    - Forced JLCPCB identical parts grouping on C1/C2/C3 and R1/R2/R3
    - Updated gerbers.zip
2026-03-08 chore(pcb): cleanup components and final manufacturing package regeneration
    - Merged manual user footprint updates for SC7A20H, TC2030, tooling holes, and battery
    - Regenerated strictly-grouped JLCPCB BOM
    - Corrected CPL metric scale
    - Removed old/unused component library files
2026-03-08 fix(pcb): update BT1 value to BAT-HLD-001 and strictly format JLCPCB/Neoden YY1 PnP CSVs
    - Changed battery holder (BT1) Comment/Value from CR-2032 to MPN BAT-HLD-001
    - Regenerated mm-scale Pick and Place data utilizing custom Neoden YY1 and JLC parsers
    - Wiped old unneeded tracked python scripts
2026-03-08 fix(pcb): repair JLCPCB CPL layer casing to strictly match Title Case
2026-03-08 Mar8 order
2026-03-09 Added CS trace and updated battery.
2026-03-26 Integrate USART1 diagnostic port on PC2/PC3 to allow serial debugging of SC7A20 sensor
2026-03-26 Patch I2C driver: Enable internal pull-ups to alleviate external hardware omission and add dynamically responsive I2C address scanner.
2026-03-26 Implement dynamic persistence-of-vision visualizer utilizing float atan2f trigonometry to map physical gravity angles to the LED ring.
2026-03-26 Optimize POV sweeps to 200us TIM2 execution rate, suppress UART printf blocks, and configure rotational offset for gravity tracking mapping.
2026-03-26 Fix SDCC loop optimizer warning by refactoring rotation offset mapping into a single modulo operation.
2026-03-26 Enhance planar POV sequencer: Reorganize resting dot loop mathematically to distribute perfectly +9 skips across all 90 unique LED array addresses symmetrically.
2026-03-26 Finalize HALO-90 Hardware Revisions and Firmware POV Optimization: - Synchronized PCB project configuration and generated manufacturing position exports. - Completed HALO-90 firmware: Integrated SC7A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
2026-04-03 Firmware: Implement EXTI wake recovery and accelerometer I2C optimizations
    - Add I/O re-initialization routine upon EXTI wake-up (magnet removed) to restore LED matrix multiplexing and UART.
    - Introduce organic fixed-point low-pass filters (LPF) for smoothing the POV base angle and LED width mapping.
    - Optimize SC7A20 accelerometer I2C reads by switching to a robust multi-byte block transfer (auto-increment).
    - Tighten I2C accel_write_reg constraints to definitively block until the physical STOP condition clears.
2026-06-21 Added mic and rerouted
2026-06-24 Implement fast Balance Halo firmware
    Add a motion-reactive Balance Halo renderer driven by accelerometer tilt and jolt energy.
    Replace blocking ISR brightness delays with temporal PWM gating, restore flat ring sweep mode, and avoid expensive hot-path modulo and 32-bit math where practical.
    Add spring-damped angular inertia, explicit jolt burst shockwaves, and four orbiting spark particles so motion charges the halo and decays back to a calm ring.
2026-06-24 Improve firmware build workflow
    Prefer the bundled SDCC toolchain when present while still allowing LDCC overrides.
    Make clean idempotent, mark debug as phony, reuse BUILDDIR consistently, and support a local stm8flash with common Homebrew libusb paths.
    Update the README TODO items for the fixed shutdown LED and HALO high-low pattern issues.
2026-06-24 Use scan-density PWM for Balance Halo breathing
    Replace the global brightness gate with an interleaved ring scanner that visits every 10th LED before moving to the next bank.
    Compute a PWM density per scanned LED so breathing, gravity glow, shimmer, sparks, and burst waves are expressed as how many scan passes each LED is lit during a brightness period.
    Keep a small calm brightness floor so the resting halo stays visible while still breathing through PWM.
2026-06-24 Make Balance Halo visibly accelerometer driven
    Remove the flat-mode render bypass so the gravity/bubble lobe is always visible instead of disappearing when X/Y tilt is modest.
    Retune the lobe as a bubble-level highlight opposite the gravity projection, with a lower base PWM floor and stronger glow contrast.
    Lower jolt thresholds and increase energy gain so steps fragment the ring earlier, spawn bursts sooner, and create more chaotic spark activity.
2026-06-24 Add UART accelerometer diagnostics
    Enable an accelerometer diagnostic build that reports boot and wake I2C configuration over UART, including address, WHO_AM_I, CTRL_REG1, CTRL_REG4, and status.
    Print periodic raw X/Y/Z samples with read success/failure counts and derived motion state so serial monitoring can confirm whether the sensor is returning live data.
    Warn when no I2C device is found or when accelerometer control bits suggest axes, ODR, or BDU are not configured.
2026-06-29 Add dim breathing still mode
    Introduce an explicit still_mode path for the HALO-90 LED renderer so a motionless board settles into a low-duty breathing state instead of keeping the bright bubble, shimmer, burst, and spark effect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
    Raise the accelerometer jolt deadzone from the previous small noise filter to a named JOLT_DEADZONE, and enter still_mode when energy has decayed below STILL_ENERGY_THRESHOLD with no active jolt. Thi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
    Start and wake at brightness 2 with still_mode enabled, then let real movement restore the existing active behavior. While still_mode is active, the ISR leaves only the base breathing br
2026-06-29 Reduce motion response sensitivity
    Add a smoothed motion_charge accumulator between accelerometer jolts and visual energy. Instead of feeding each active jolt directly into energy, motion now has to accumulate past MOTION_CHARGE_START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
    Scale jolt input by MOTION_CHARGE_SCALE_DIVISOR=5, reducing sensitivity by 80%. This keeps small bumps and isolated steps from immediately pushing the LEDs into the active high-brightness behavior, w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
    Make bursts and orbiting sparks depend on accumulated charge via MOTION_CHARGE_BURST, so one-off jolts do not trigger the most energetic effects. Reset motion_charge on wake

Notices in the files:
firmware/src/halo.c:
Copyright (C) 2021 Kolibri - Sawaiz Syed
This program is free software: you can redistribute it and/or modify
it under the terms of the GNU General Public License as published by
the Free Software Foundation, either version 3 of the License, or
(at your option) any later version.
readme.md:
[CERN-OHL-S]: ./pcb/LICENSE
[GNU GPL]: ./firmware/LICENSE
[CC BY-SA]: ./docs/LICENSE
